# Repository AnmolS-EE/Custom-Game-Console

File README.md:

# Custom ESP32 Arcade Console (V1.0)

An arcade-style game console built around the ESP32 microcontroller featuring a custom 2-layer PCB, OLED display, joystick input, tactile buttons, buzzer feedback, and multi-color LED's.

## Hardware Features
* **Microcontroller:** ESP32-WROOM-32
* **Display:** 0.96" I2C OLED Display
* **Controls:** 2-axis analog joystick + 4 tactile push buttons
* **Feedback:** Active buzzer for game audio + 4 status LEDs
* **Power:** Custom 2-layer PCB designed in KiCad

### Schematic

### 3D PCB View

## Project Evolution: Breadboard to PCB
The project began as a fully functional breadboard prototype used to validate:

* GPIO pin mapping
* joystick input behavior
* display communication (I2C)
* game state transitions
* buzzer and LED feedback logic

### Breadboard Prototype
]

After successful testing, the system was transferred to a custom PCB designed in KiCad, focusing on clean signal routing, reliable power delivery, and compact system integration. 

### Assembled Hardware

The final manufactured board has been created and the components have been soldered on. This transformed the initial breadboard concept into a robust, standalone device. You can watch a small edit of the soldering and final assembly process in my [TikTok build video](https://www.tiktok.com/@anmol.ee/video/7637941595454639381?is_from_webapp=1&sender_device=pc&web_id=7633530922164045320).

## Firmware & Logic
Firmware was developed using C++ (Arduino IDE) on the ESP32 development board.
The software architecture supports multiple programmable games with modular input handling, display rendering, state management, and sound feedback.

## Future Improvements (V2.0)
While version 1.0 successfully validates the core hardware and software architecture, future versions will focus on a more clean and consumer-ready design. Planned improvements include:

* **Component Integration:** Transitioning away from bulky pre-packaged modules by designing custom footprints to mount a bare joystick and buzzer directly onto the PCB.
* **Enhanced Display:** Upgrading to a larger OLED screen for improved visibility and addition of color.
* **Layout Optimization:** Refining the PCB trace routing and component placement for an even cleaner and more efficient board design.
* **Custom Enclosure:** Designing and 3D printing a custom case to house the console, improve handling, and protect the exposed circuitry.

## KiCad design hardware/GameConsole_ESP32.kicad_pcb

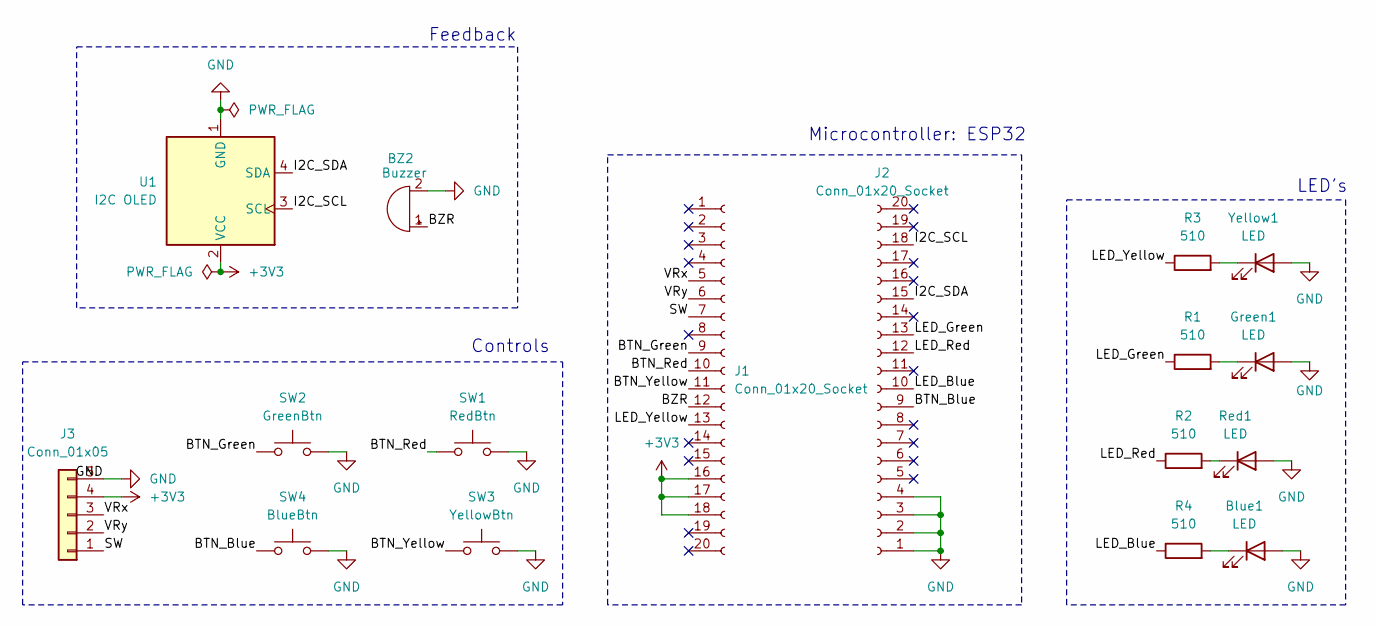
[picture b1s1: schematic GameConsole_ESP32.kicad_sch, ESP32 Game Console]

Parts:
BZ2: Buzzer; CP_Radial_D12.5mm_P5.00mm
Blue1: LED; LED_D3.0mm
Green1: LED; LED_D3.0mm
J1, J2: Conn_01x20_Socket; PinSocket_1x20_P2.54mm_Vertical
J3: Conn_01x05; PinSocket_1x05_P2.54mm_Horizontal
R1, R2, R3, R4: 510; R_Axial_DIN0207_L6.3mm_D2.5mm_P10.16mm_Horizontal
Red1: LED; LED_D3.0mm
SW1: RedBtn; SW_PUSH_6x6mm_2Pin_P5.08mm
SW2: GreenBtn; SW_PUSH_6x6mm_2Pin_P5.08mm
SW3: YellowBtn; SW_PUSH_6x6mm_2Pin_P5.08mm
SW4: BlueBtn; SW_PUSH_6x6mm_2Pin_P5.08mm
U1: I2C OLED; miniOLED
Yellow1: LED; LED_D3.0mm

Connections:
+3V3: J1.16, J1.17, J1.18, J3.4, U1.2 (VCC)
/BTN_Blue: J2.9, SW4.1
/BTN_Green: J1.9, SW2.1
/BTN_Red: J1.10, SW1.1
/BTN_Yellow: J1.11, SW3.1
/BZR: BZ2.1 (+), J1.12
/I2C_SCL: J2.18, U1.3 (SCL)
/I2C_SDA: J2.15, U1.4 (SDA)
/LED_Blue: J2.10, R4.1
/LED_Green: J2.13, R1.1
/LED_Red: J2.12, R2.1
/LED_Yellow: J1.13, R3.1
/SW: J1.7, J3.1
/VRx: J1.5, J3.3
/VRy: J1.6, J3.2
GND: BZ2.2 (-), Blue1.2 (A), Green1.2 (A), J2.1, J2.2, J2.3, J2.4, J3.5, Red1.2 (A), SW1.2, SW2.2, SW3.2, SW4.2, U1.1 (GND), Yellow1.2 (A)
unnamed: Blue1.1 (K), R4.2
unnamed: Green1.1 (K), R1.2
unnamed: R2.2, Red1.1 (K)
unnamed: R3.2, Yellow1.1 (K)

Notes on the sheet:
Microcontroller: ESP32
LED's
Controls
Feedback

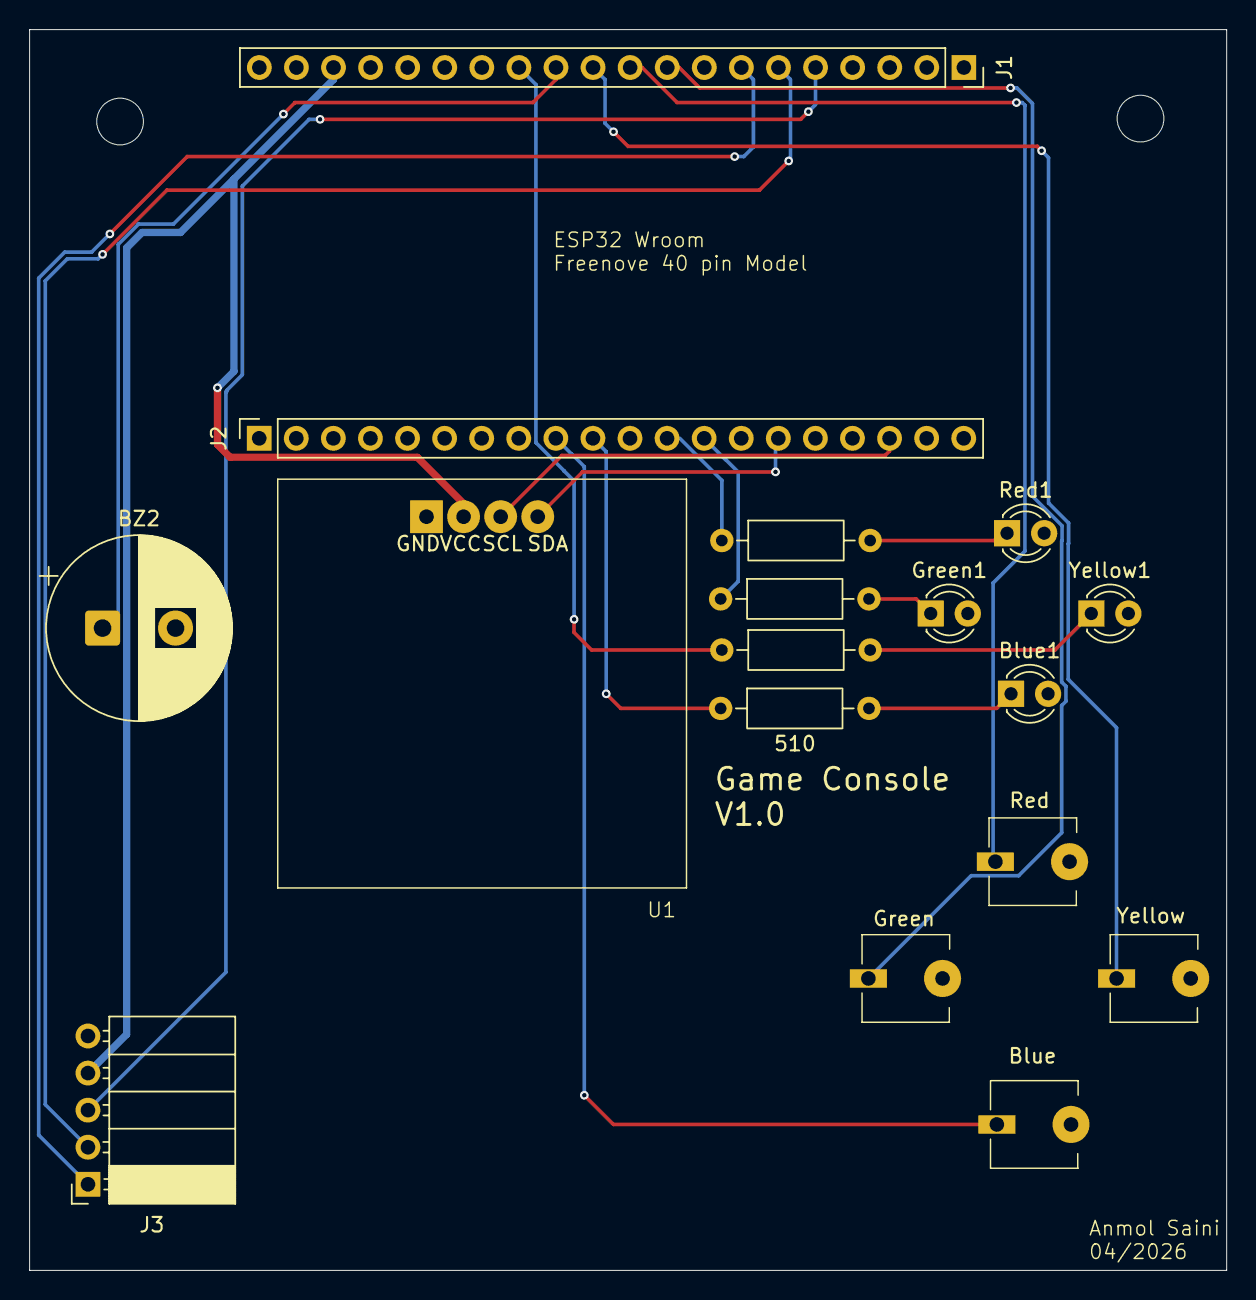
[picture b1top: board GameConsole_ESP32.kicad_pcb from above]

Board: 2 copper layers, 82.0 x 85.0 mm, 17 parts (0 on the bottom side), 20 nets.

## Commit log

2026-04-27 Create .gitignore to manage ignored files
    Add a .gitignore file to exclude build files, KiCad backups, and OS-generated junk files.
2026-04-27 Initial V1.0 KiCad schematic and PCB layout
2026-04-27 Revise README with detailed project information
    Expanded project description and added hardware features, project evolution details, firmware information, and upcoming improvements.
2026-04-27 Add initial ESP32 game firmware.
2026-04-27 Breadboard prototype photo.
2026-04-27 Add initial 3D PCB design.
2026-04-28 Cleaned up schematic and updated PCB design
2026-04-29 Updated images
2026-04-29 Enhance README with schematic and PCB views
    Added schematic and 3D PCB view images to README.
2026-05-09 Uploading fully assembled PCB.
2026-05-09 Update README with assembled hardware and future plans
    Added details about the assembled hardware and future improvements.
2026-05-09 Fix image link and update firmware description
    Updated image link formatting and clarified firmware development environment.
